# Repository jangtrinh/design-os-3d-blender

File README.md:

# DESIGN:OS 3D Blender Agent (`design-os-3d-blender`)

<!-- mcp-name: io.github.jangtrinh/design-os-3d-blender -->

**Parametric 3D mechanical parts generator, headless Blender Python (`bpy`) pipeline, and embedded Three.js CAD showcase engine.**

Generate dimensionally accurate gears, enclosures, drone frames, and exploded mechanical assemblies from plain-English specs or JSON parameters, complete with glTF/STL exports and interactive browser inspection.

**design-os-3d-blender is a free MCP server** (Model Context Protocol, stdio) for Blender. Connect it to Claude Code, Codex, Cursor or any MCP client to model, render and verify parts in Blender 5.2 LTS. Free, nothing sold, source-available under PolyForm Shield 1.0.0.

<p align="center">

</p>

<p align="center">
  <a href="#quickstart">Quickstart</a> · <a href="#what-it-makes">What it makes</a> · <a href="#installation">Install</a> · <a href="#how-it-works">How it works</a> · <a href="#commands--diagnostics">Commands</a> · <a href="#quality-bar--limitations">Limits</a>
</p>

---

## Why this exists

Text-to-3D diffusion models produce melted, non-manifold blobs that cannot be 3D-printed, machined, or cleanly animated in web viewers. **`design-os-3d-blender`** drives Blender's Python API (`bpy`) and Three.js deterministically to produce crisp mechanical geometry and interactive CAD showcases.

| Dimension | Generic AI / Manual Workflow | DESIGN:OS 3D Blender Agent (`DESIGN:OS`) |
| :--- | :--- | :--- |
| **Geometry Quality** | Melted AI diffusion meshes with non-manifold holes | Clean parametric `bpy` booleans, bevels, and precision vertex topology |
| **Dimensional Accuracy** | Arbitrary unscaled units that fail in slicers | Millimeter-locked parametric dimensions and bounding-box verification |
| **Web Inspection** | Static screenshots with no way to inspect hidden faces | Embedded Three.js CAD viewer with orbit controls, wireframe, and exploded scrub |
| **Reproducibility** | Unrepeatable random seeds | Git-tracked Python generator scripts and declarative JSON part specs |
| **Privacy & Telemetry** | Opaque cloud telemetry or unverified third-party APIs | **Zero telemetry** — 100% local execution ([`PRIVACY.md`](PRIVACY.md) audited) |

---

## Quickstart

### 1. Install the plugin or CLI

**In Claude Code:**

```text
/plugin marketplace add jangtrinh/design-os-3d-blender
/plugin install design-os-3d-blender@design-os-3d-blender
```

**Or from your terminal (Codex, Gemini CLI, Antigravity, OpenCode, or standalone CLI):**

```bash
git clone https://github.com/jangtrinh/design-os-3d-blender.git
cd design-os-3d-blender
python3 scripts/self_check.py
```

### 2. Ask in plain English

Open your project in your AI coding agent and describe what you need:

> "Generate a parametric 24-tooth helical gear and mounting bracket in headless Blender and export glTF + STL artifacts."

> "Build an interactive Three.js CAD viewer page with exploded-view scrubbing, wireframe toggle, and orthographic camera presets."

> "Audit the exported mesh topology for non-manifold edges, zero-area faces, and bounding-box dimensional tolerances."

### 3. Verify your setup

```bash
python3 scripts/self_check.py
```

---

## What it makes

Every deliverable produced by `design-os-3d-blender` is backed by a deterministic verification gate rather than freehand AI guesswork.

<p align="center">
  <br>
  <sub>Prompt: <code>"Generate a parametric 24-tooth helical gear and mounting bracket in headless Blender and export glTF + STL artifacts."</code></sub>
</p>

| Deliverable / Mode | Best for | Output Format | Verification Gate |
| :--- | :--- | :--- | :--- |
| **Parametric `bpy` Part Scripts** | Reproducible headless Blender generation for brackets, gears, and housings | `Python (.py) + JSON spec` | `Zero non-manifold edges` |
| **Print & Web 3D Assets** | Exporting production meshes for 3D printing and real-time web rendering | `.glb / .gltf / .stl / .obj` | `Bounding-box & file integrity check` |
| **Three.js CAD Showcase** | Interactive browser viewer with material switches and exploded assembly scrub | `Self-contained HTML + Three.js` | `60fps WebGL render check` |

---

## Installation

Choose the setup that matches your AI coding agent. Every option installs the same canonical skill (`skills/design-os-3d-blender/SKILL.md`) and `/doctor` diagnostic suite.

### Claude Code

Run these two commands inside Claude Code:

```text
/plugin marketplace add jangtrinh/design-os-3d-blender
/plugin install design-os-3d-blender@design-os-3d-blender
```

### OpenAI Codex

Install to your personal Codex skills directory:

```bash
git clone https://github.com/jangtrinh/design-os-3d-blender.git /tmp/design-os-3d-blender
mkdir -p ~/.codex/skills/design-os-3d-blender ~/.codex/prompts
cp -R /tmp/design-os-3d-blender/skills/design-os-3d-blender/* ~/.codex/skills/design-os-3d-blender/
cp /tmp/design-os-3d-blender/prompts/doctor.md ~/.codex/prompts/design-os-3d-blender-doctor.md
rm -rf /tmp/design-os-3d-blender
```

### Gemini CLI & Google Antigravity

```bash
git clone https://github.com/jangtrinh/design-os-3d-blender.git /tmp/design-os-3d-blender
mkdir -p ~/.gemini/skills/design-os-3d-blender
cp -R /tmp/design-os-3d-blender/skills/design-os-3d-blender/* ~/.gemini/skills/design-os-3d-blender/
rm -rf /tmp/design-os-3d-blender
```

### OpenCode, Cursor, Windsurf & Other Agent Harnesses

```bash
git clone https://github.com/jangtrinh/design-os-3d-blender.git /tmp/design-os-3d-blender
mkdir -p ~/.agents/skills/design-os-3d-blender
cp -R /tmp/design-os-3d-blender/skills/design-os-3d-blender/* ~/.agents/skills/design-os-3d-blender/
rm -rf /tmp/design-os-3d-blender
```

<details>
<summary>Verify or uninstall</summary>

**Verify installation:**

```bash
python3 scripts/self_check.py
```

Or run `/doctor` inside Claude Code / Codex to inspect installed skill paths, plugin manifests, and gate health.

**Uninstall:**

```bash
rm -rf ~/.claude/skills/design-os-3d-blender ~/.codex/skills/design-os-3d-blender ~/.gemini/skills/design-os-3d-blender ~/.agents/skills/design-os-3d-blender
```

</details>

---

## Usage & Prompt Cookbook

Once installed, `skills/design-os-3d-blender/SKILL.md` activates automatically when your prompt matches its domain triggers. Browse [`docs/cookbook.md`](docs/cookbook.md) for copy-paste prompt recipes.

**Generate & Scaffold**

```text
"Generate a parametric 24-tooth helical gear and mounting bracket in headless Blender and export glTF + STL artifacts."
```

**Audit & Verify**

```text
"Build an interactive Three.js CAD viewer page with exploded-view scrubbing, wireframe toggle, and orthographic camera presets."
```

**Export & Automate**

```text
"Audit the exported mesh topology for non-manifold edges, zero-area faces, and bounding-box dimensional tolerances."
```

---

## Commands & Diagnostics

| Command | Environment | What it does |
| :--- | :--- | :--- |
| `/doctor` | Claude Code / Codex | Read-only diagnostic check of installed skill paths, plugin manifests, and runtime prerequisites |
| `python3 scripts/self_check.py` | Terminal / CI | Deterministic offline verification of manifests, skill contracts, and governance files |
| `python3 scripts/self_check.py` | Terminal / CI | Verify 3D Blender skill contracts, CAD showcase assets, and repository delivery manifests |

---

## How it works

1. **Intent Routing** — Your AI agent matches your request against `skills/design-os-3d-blender/SKILL.md` frontmatter triggers.
2. **Progressive Context Loading** — Only the entry-point `SKILL.md` router loads initially; detailed recipes and scripts load on demand.
3. **Deterministic Execution** — Domain scripts and contracts execute locally with reproducible inputs and outputs.
4. **Gate Verification** — `scripts/self_check.py` and domain verifiers (`python3 scripts/self_check.py`) validate the artifact before completion.
5. **Zero-Telemetry Delivery** — Verified files are written directly to your workspace with zero external network calls.

```text
User Prompt / CLI Invocation
            │
            ▼
┌───────────────────────────────────────────────┐
│ skills/design-os-3d-blender/SKILL.md
│ Progressive disclosure router & hard rules    │
└───────────┬───────────────────────────────────┘
            │ loads on demand
            ▼
┌───────────────────────────────────────────────┐
│ python3 scripts/self_check.py
│ Deterministic build & contract enforcement    │
└───────────┬───────────────────────────────────┘
            │ verifies
            ▼
┌───────────────────────────────────────────────┐
│ python3 scripts/self_check.py + /doctor       │
│ Zero-telemetry local verification gate        │
└───────────────────────────────────────────────┘
```

### What loads when

`design-os-3d-blender` uses progressive context disclosure so your agent's context window stays fast and focused:

| File | Loaded when |
| :--- | :--- |
| `skills/design-os-3d-blender/SKILL.md` | Always (~100–150 lines) — routing rules, triggers, and execution workflow |
| `docs/cookbook.md` | When selecting multi-step prompt recipes or domain patterns |
| `commands/doctor.md` / `prompts/doctor.md` | Only when running `/doctor` diagnostics |
| `llms.txt` | When indexed by AI answer engines, RAG pipelines, or repo crawlers |

---

## File structure

```text
design-os-3d-blender/
├── .claude-plugin/
│   ├── plugin.json                 # Claude Code plugin manifest
│   └── marketplace.json            # Claude Code marketplace catalog
├── .codex-plugin/
│   └── plugin.json                 # OpenAI Codex plugin & interface manifest
├── .agents/
│   └── plugins/marketplace.json    # Cross-agent local plugin registry
├── .factory-plugin/
│   ├── plugin.json                 # Factory / Droid plugin manifest
│   └── marketplace.json            # Factory marketplace metadata
├── skills/
│   └── design-os-3d-blender/
│       └── SKILL.md                # Canonical agent skill entrypoint
├── commands/
│   └── doctor.md                   # /doctor diagnostic slash command
├── prompts/
│   └── doctor.md                   # Codex diagnostic prompt mirror
├── scripts/
│   └── self_check.py               # Deterministic repository & skill self-check
├── docs/
│   ├── cookbook.md                 # Copy-paste prompt recipes by job
│   └── llms.txt                    # GEO / LLM discovery index
├── PRIVACY.md                      # Zero-telemetry & local-first privacy commitment
├── SECURITY.md                     # Vulnerability disclosure & security policy
├── CONTRIBUTING.md                 # Contribution workflow & verification rules
├── CODE_OF_CONDUCT.md              # Contributor Covenant code of conduct
├── CHANGELOG.md                    # Release history
├── llms.txt                        # Root LLM indexing manifest
├── LICENSE                         # PolyForm Shield 1.0.0
└── README.md
```

---

## Quality bar & Limitations

### It's working if...

- `python3 scripts/self_check.py` prints `ok: design-os-3d-blender self-check passed (design-os-3d-blender)` and exits `0`.
- `python3 scripts/self_check.py` passes with zero contract or test regressions.
- Your AI coding agent loads `skills/design-os-3d-blender/SKILL.md` automatically when given any prompt from [`docs/cookbook.md`](docs/cookbook.md).
- Network traffic during execution remains zero (guaranteed by [`PRIVACY.md`](PRIVACY.md)).

### When not to use

- Sheet-metal or paperboard folding dielines where 2D crease patterns govern topology (use `design-os-origami`).
- Organic character sculpting or AAA rigged game characters requiring manual ZBrush artistry.
- 2D vector UI motion walkthroughs (use `design-os-svg-animation`).

---

## DESIGN:OS Ecosystem

`design-os-3d-blender` is one of the 13 source-available engines in the **`DESIGN:OS`** ecosystem:

| Engine | Live Docs | Repository | Layer |
| :--- | :--- | :--- | :--- |
| **DESIGN:OS CLI** | [jangtrinh.github.io/design-os](https://jangtrinh.github.io/design-os/) | [`jangtrinh/design-os`](https://github.com/jangtrinh/design-os) | `cli` |
| **Knowledge Builder** | [jangtrinh.github.io/design-os-knowledge-builder](https://jangtrinh.github.io/design-os-knowledge-builder/) | [`jangtrinh/design-os-knowledge-builder`](https://github.com/jangtrinh/design-os-knowledge-builder) | `compiler` |
| **Figma Plugin & CLI** | [jangtrinh.github.io/design-os-figma-plugin](https://jangtrinh.github.io/design-os-figma-plugin/) | [`jangtrinh/design-os-figma-plugin`](https://github.com/jangtrinh/design-os-figma-plugin) | `plugin` |
| **SVG Animation Engine** | [jangtrinh.github.io/design-os-svg-animation](https://jangtrinh.github.io/design-os-svg-animation/) | [`jangtrinh/design-os-svg-animation`](https://github.com/jangtrinh/design-os-svg-animation) | `engine` |
| **3D Blender Agent** | [jangtrinh.github.io/design-os-3d-blender](https://jangtrinh.github.io/design-os-3d-blender/) | [`jangtrinh/design-os-3d-blender`](https://github.com/jangtrinh/design-os-3d-blender) | `3d / cad` |
| **OPAH ONE Drone** | [jangtrinh.github.io/design-os-drone-showcase](https://jangtrinh.github.io/design-os-drone-showcase/) | [`jangtrinh/design-os-drone-showcase`](https://github.com/jangtrinh/design-os-drone-showcase) | `hardware` |
| **GitHub Pages Engine** | [jangtrinh.github.io/design-os-github-page](https://jangtrinh.github.io/design-os-github-page/) | [`jangtrinh/design-os-github-page`](https://github.com/jangtrinh/design-os-github-page) | `pages` |
| **Apple Design OS** | [jangtrinh.github.io/design-os-apple](https://jangtrinh.github.io/design-os-apple/) | [`jangtrinh/design-os-apple`](https://github.com/jangtrinh/design-os-apple) | `swiftui` |
| **Agent Teacher** | [jangtrinh.github.io/design-os-pedagogy](https://jangtrinh.github.io/design-os-pedagogy/) | [`jangtrinh/design-os-pedagogy`](https://github.com/jangtrinh/design-os-pedagogy) | `pedagogy` |
| **Origami CAD** | [jangtrinh.github.io/design-os-origami](https://jangtrinh.github.io/design-os-origami/) | [`jangtrinh/design-os-origami`](https://github.com/jangtrinh/design-os-origami) | `packaging` |
| **Voice UX Architecture** | [jangtrinh.github.io/design-os-voice-ux](https://jangtrinh.github.io/design-os-voice-ux/) | [`jangtrinh/design-os-voice-ux`](https://github.com/jangtrinh/design-os-voice-ux) | `voice-ai` |
| **Code2Flow** | [jangtrinh.github.io/design-os-code2flow](https://jangtrinh.github.io/design-os-code2flow/) | [`jangtrinh/design-os-code2flow`](https://github.com/jangtrinh/design-os-code2flow) | `ast / audit` |
| **Generative UI** | [jangtrinh.github.io/design-os-generative-ui](https://jangtrinh.github.io/design-os-generative-ui/) | [`jangtrinh/design-os-generative-ui`](https://github.com/jangtrinh/design-os-generative-ui) | `runtime` |

---

## Contributing, Governance & License

- **Contributing**: See [`CONTRIBUTING.md`](CONTRIBUTING.md) for pull request guidelines and verification gates (`python3 scripts/self_check.py`).
- **Code of Conduct**: Governed by [`CODE_OF_CONDUCT.md`](CODE_OF_CONDUCT.md).
- **Security & Privacy**: Zero telemetry — see [`SECURITY.md`](SECURITY.md) and [`PRIVACY.md`](PRIVACY.md).
- **Changelog & LLM Index**: Track releases in [`CHANGELOG.md`](CHANGELOG.md) and machine-readable index in [`llms.txt`](llms.txt).
- **License**: [PolyForm Shield 1.0.0](LICENSE) © [Jang Trinh](https://github.com/jangtrinh). Free to use and modify, including for paid client work; you may not resell it or build a competing product from it.

---

## Watch

A FREE, source-available (PolyForm Shield) agent pipeline for Blender 5.2. Videos from the [design:os by Jang](https://www.youtube.com/@designosbyjang) channel (Vietnamese, with English terms):

<p align="left">

</p>

- [How to use design os 3d blender repo - ep 1](https://www.youtube.com/watch?v=J2Malrlb_PM) (2:57): Episode 1: building a keyboard (CK-001) end to end with design-os-3d-blender: photo, spec, gates, STL and GLB export. Vietnamese.
- [How to use design os 3d blender repo - ep 2](https://www.youtube.com/watch?v=LKL7ZHMz5KI) (5:34): Episode 2: the DC-01 desk robot with 29 mechanical revisions, four gated runs and a printable kit. Vietnamese.
- [Fanmade 3D model for Nowa planet - by design os 3d blender](https://www.youtube.com/watch?v=XSKZYudfMt8) (0:27): 27-second fan-made 3D model of the Nowa desktop product, built with design-os-3d-blender.

More: [design:os by Jang on YouTube](https://www.youtube.com/@designosbyjang).

---

## Listed on

<p align="left">

</p>

Also listed in the [Official MCP Registry](https://registry.modelcontextprotocol.io/v0/servers?search=design-os-3d-blender) (`io.github.jangtrinh/design-os-3d-blender`), the [awesome-mcp-servers list by TensorBlock](https://github.com/TensorBlock/awesome-mcp-servers/blob/main/docs/art-culture--media.md) and [SkillsMP](https://skillsmp.com/creators/jangtrinh).

---

If `design-os-3d-blender` saves you time, a star on GitHub helps other engineers and AI agents find it.

<p align="left">
  
</p>

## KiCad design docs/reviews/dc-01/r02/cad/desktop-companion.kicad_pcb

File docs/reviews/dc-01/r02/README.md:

# DC-01 native engineering demo

Open `index.html` in a browser. The page and media work offline. The MP4 has no audio.

## Included deliverables

| File | Content |
|---|---|
| `dc01-native-animatic.mp4` | 120 original 1920 × 1080 Blender poses, held at selected chapters for a 39-second review; encoded at30fps by repeating frames, not synthesized in-between motion |
| `native/dc01-demo.blend` | Editable saved animation with the assembly at frame1 |
| `native/dc01-assembly.blend` | Full H13 assembly with all26 routed base connections |
| `native/dc01-engineering.blend` | Frozen I06 mechanical/electronic/control assembly before harness |
| `DC01-P03-print-kit.zip`, `print/` |18 STL parts, two core3MF plates, native print bake and source-bound checks |
| `electronics/` | Editable KiCad schematic/PCB and local libraries, BOMs, pin/wire maps, actual Gerber/Excellon candidates and native ERC/DRC records |
| `reports/` | Original revision-bound reports for geometry, wiring, print, animation and video |

## What the demonstration establishes

I06 has18 passing printable-part forms and an explicit per-part coverage audit. The exported P03 parts preserve the native source geometry under declared axis rotations. Both core3MF files were independently reopened; all triangles match the gated STL files.17 PETG parts and one TPU diaphragm are separated by material.

H13 has26 complete base connections comprising27 wire legs because the positive pack lead is split at the fuse. Reopened native curves were checked against252 static obstacles and every other installed wire. Independent curvature extrema and both sides of curve joins retain the3mm minimum-radius requirement. These are static geometry results, not a material or service-flexing test.

The native animation preserves1461 original mesh/curve basis geometries and uses29 catalog groups. Many mesh objects are copper, pads or other subdivisions of one physical part. Frame1,86 and102 restore the same assembled matrices. Side screws withdraw before the upper assembly lifts. Wires are omitted during the disconnected service phase and displayed separately in the explanatory catalog.

## Fixed construction and authored behavior

Arms and ears are fixed retained cosmetic parts. The feet are integral in the lower shell. There is no powered arm/ear joint or walking mechanism. Display blinking/looking and button displacement are authored illustrations; no firmware binary, measured button force, spring return, fatigue or safe overtravel is demonstrated. Audio is unpopulated.

The exploded catalog is an explanation of the same source parts, not a qualified factory assembly path. A grouped hardware cluster and small edge-on parts are overview limitations. Dedicated detail views, when included under `stills/details/`, state their hidden and translated objects separately. Exact photographic fidelity is not accepted: exposed fasteners, the visor and sharper edge/seam transitions differ from the original concept.

## Print and electrical status

**Digital geometry/export checks: complete in the recorded scope. Physical manufacture and battery operation: BLOCKED. Physical sample count:0.**

P03 contains geometry-only3MF files, not printer profiles, supports or G-code. Follow `print/README.md`: keep scale100%, assign actual PETG/TPU profiles, inspect support/brim space and evaluate first-layer contact. The18 meshes in `print/print.blend` retain original datums; the3MF build-item translations produce the plate layouts. Do not print the source-only scene or rotate parts twice.

The custom board is a carrier for a purchased ESP32-S3 module, not custom silicon. Native KiCad A04 reports0 ERC violations and0 DRC violations, unconnected items or schematic-parity issues. Actual passive/connector selection, battery lot/polarity, charge-temperature limits, operating undervoltage behavior, lead-fuse coordination, rails/transients, closed-case temperature, firmware and RF trials remain open.13 harness endpoints remain placement/termination proposals. See `electronics/bench-validation.md` and `reports/harness/handoff.json`.

The installed raised charger screw cannot be reached by the modeled driver and must be tightened during preassembly. The source service sequence records tested sampled poses and a detected former collision. Continuous transit, physical tools, tightening torque and wiring service movement are not established.

## Source pins and reproducibility

Full assembly: `526b2ca2822be17287f49f6fd3682295e700f269b11ade47891f94b5bbe67ab9`

Native animation: `5562660ab43d6cae029b5a8b439c47e4f3704a538546636bd026c22f918524cd`

MP4: `d9b937f4eafc427c39a8a9aef4b26c948c2b8cfb82e17b1a77aad4745c8a2780`

`manifest.json` and `SHA256SUMS` identify the delivered bytes. From this directory, run `shasum -a256 -c SHA256SUMS`. Original reports retain their original Mac workspace paths and hashes; package copies are separately listed in the delivery manifest. Reproduction scripts remain in the project's `builds/desktop-companion` workspace; the editable Blender/CAD files are included here. The120 raw native frames are preserved in `presentation/D05/native-frames` in that workspace and are not duplicated in this compact archive.

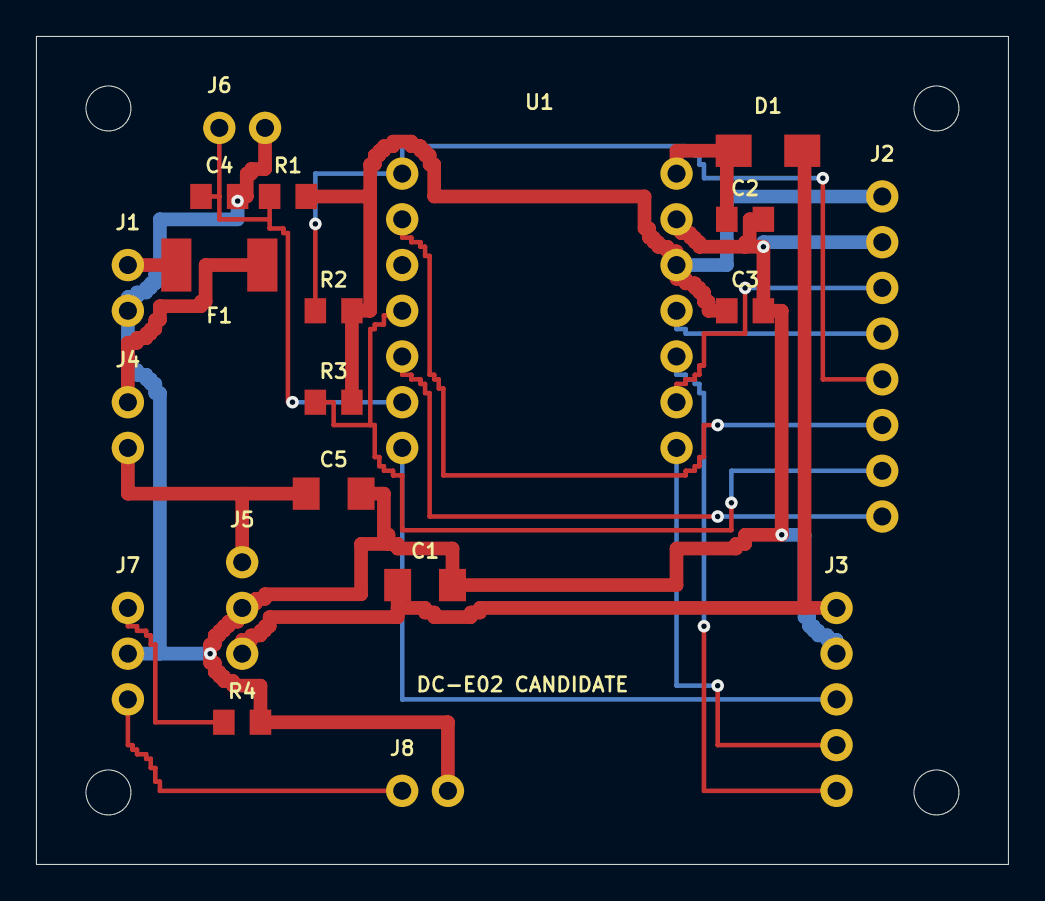
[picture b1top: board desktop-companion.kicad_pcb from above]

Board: 2 copper layers, 54.0 x 46.0 mm, 24 parts (0 on the bottom side), 19 nets.

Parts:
C1: 47uF_10V_X5R; C1
C2: 100nF_16V_X7R; C2
C3: 10uF_10V_X5R; C3
C4: 100nF_16V_X7R; C4
C5: 47uF_10V_X5R; C5
D1: SS14_SCHOTTKY; D1
F1: MF-MSMF110_16X-2; F1
H1, H2, H3, H4: M2_CLEARANCE
J1: BQ24074_OUT; J1
J2: DISPLAY_5206; J2
J3: I2S_AUDIO_OPTION; J3
J4: POWER_SWITCH; J4
J5: S7V8F5_WIRED; J5
J6: MOMENTARY_BUTTON; J6
J7: CHARGER_PROGRAM_NTC; J7
J8: 103AT2_PACK_SENSOR; J8
R1: 10k_1%; R1
R2: 10k_1%; R2
R3: 10k_1%; R3
R4: 3.57k_1%; R4
U1: Seeed_XIAO_ESP32S3_nonSense; U1

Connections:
+3V3: C3.1, J2.1, R1.2, R2.2, R3.2, U1.12
+5V: C1.1, D1.2, J3.1, J5.3
BUTTON_N: C4.1, J6.1, R1.1, U1.6
COMPUTE_5V: C2.1, D1.1, U1.14
GND: C1.2, C2.2, C3.2, C4.2, C5.2, J1.2, J2.2, J3.2, J5.2, J6.2, J7.2, J8.2, R4.2, U1.13
I2S_BCLK: J3.3, U1.7
I2S_DIN: J3.5, U1.10
I2S_LRCLK: J3.4, U1.8
ISET: J7.1, R4.1
LCD_BL: J2.8, U1.5
LCD_CS: J2.5, R2.1, U1.1
LCD_DC: J2.6, U1.2
LCD_RST: J2.7, R3.1, U1.4
NTC_TS: J7.3, J8.1
SPI_MOSI: J2.4, U1.11
SPI_SCK: J2.3, U1.9
SYS_FUSED: F1.2, J4.1
SYS_RAW: F1.1, J1.1
SYS_SW: C5.1, J4.2, J5.1

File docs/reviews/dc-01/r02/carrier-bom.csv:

Reference,Value,Package_or_interface,Quantity,Selection_status
U1,Seeed_XIAO_ESP32S3_nonSense,compute,1,Purchased compute module on removable sockets; no custom silicon design
J1,BQ24074_OUT,connector,1,2.54mm pin-header engineering interface; keyed production connector not selected
J2,DISPLAY_5206,connector,1,2.54mm pin-header engineering interface; keyed production connector not selected
J3,I2S_AUDIO_OPTION,connector,1,2.54mm pin-header engineering interface; keyed production connector not selected
J4,POWER_SWITCH,connector,1,2.54mm pin-header engineering interface; keyed production connector not selected
J5,S7V8F5_WIRED,connector,1,2.54mm pin-header engineering interface; keyed production connector not selected
J6,MOMENTARY_BUTTON,connector,1,2.54mm pin-header engineering interface; keyed production connector not selected
J7,CHARGER_PROGRAM_NTC,connector,1,2.54mm pin-header engineering interface; keyed production connector not selected
J8,103AT2_PACK_SENSOR,connector,1,2.54mm pin-header engineering interface; keyed production connector not selected
F1,MF-MSMF110_16X-2,1812,1,"Bourns MF-MSMF110/16X-2; sourced style2 land pattern; 1.10A hold at23C, 0.85A at50C; trip coordination unqualified"
D1,SS14_SCHOTTKY,SMA,1,"Vishay SS14-E3/61T candidate; pin1 cathode, pin2 anode; dedicated DO-214AC footprint"
R1,10k_1%,0805,1,Value/package candidate; MPN procurement release open
R2,10k_1%,0805,1,Value/package candidate; MPN procurement release open
R3,10k_1%,0805,1,Value/package candidate; MPN procurement release open
R4,3.57k_1%,0805,1,Value/package candidate; MPN procurement release open
C1,47uF_10V_X5R,1206,1,Value/package candidate; MPN procurement release open
C2,100nF_16V_X7R,0805,1,Value/package candidate; MPN procurement release open
C3,10uF_10V_X5R,0805,1,Value/package candidate; MPN procurement release open
C4,100nF_16V_X7R,0805,1,Value/package candidate; MPN procurement release open
C5,47uF_10V_X5R,1206,1,Value/package candidate; MPN procurement release open
